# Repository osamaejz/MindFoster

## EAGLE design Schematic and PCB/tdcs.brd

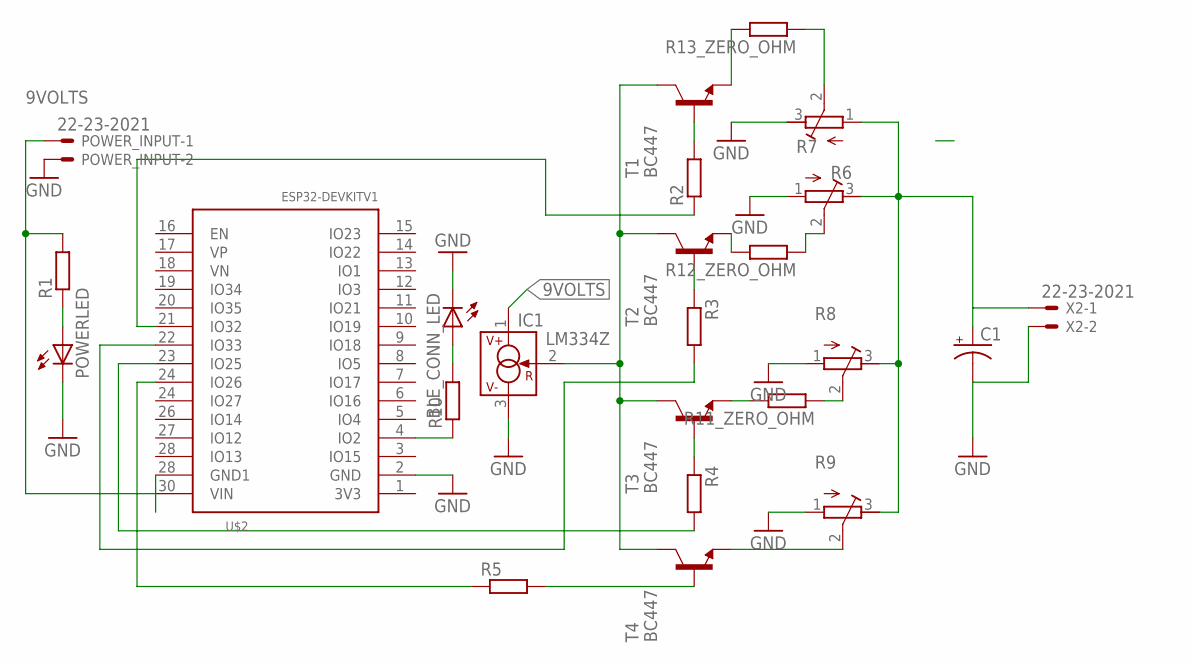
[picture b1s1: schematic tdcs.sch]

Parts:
BLE_CONN_LED: LED3MM
C1: CPOL-USE1.8-4; E1,8-4
IC1: LM334Z; TO92
POWERLED: LEDB152; Q62902-B152
POWER_INPUT: 22-23-2021
R1, R2, R3, R4, R5, R10, R11_ZERO_OHM, R12_ZERO_OHM, R13_ZERO_OHM: R-EU_0204/5; 0204/5
R6, R7, R8, R9: R-TRIMM64W; RTRIM64W
T1, T2, T3, T4: BC447; TO92-EBC
U$2: ESP32DEVKITV1; ESP32-DEVKITV1
X2: 22-23-2021

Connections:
9VOLTS: IC1.1 (V+), POWER_INPUT.1, R1.2, U$2.30 (VIN)
GND: BLE_CONN_LED.K (C), C1.-, IC1.3 (V-), POWERLED.K (C), POWER_INPUT.2, R6.3 (E), R7.1 (A), R8.1 (A), R9.1 (A), U$2.2 (GND), X2.2
unnamed: R2.2, T1.B
unnamed: R3.1, T2.B
unnamed: R4.1, T3.B
unnamed: R5.1, U$2.24 (IO27)
unnamed: IC1.2 (R), T1.C, T2.C, T3.C, T4.C
unnamed: BLE_CONN_LED.A, R10.2
unnamed: R3.2, U$2.22 (IO33)
unnamed: R4.2, U$2.23 (IO25)
unnamed: R5.2, T4.B
unnamed: R9.2 (S), T4.E
unnamed: R11_ZERO_OHM.2, T3.E
unnamed: R7.2 (S), R12_ZERO_OHM.1
unnamed: C1.+, R6.1 (A), R7.3 (E), R8.3 (E), R9.3 (E), X2.1
unnamed: R10.1, U$2.4 (IO2)
unnamed: POWERLED.A, R1.1
unnamed: R8.2 (S), R11_ZERO_OHM.1
unnamed: R12_ZERO_OHM.2, T2.E
unnamed: R13_ZERO_OHM.2, T1.E
unnamed: R6.2 (S), R13_ZERO_OHM.1
unnamed: R2.1, U$2.21 (IO32)

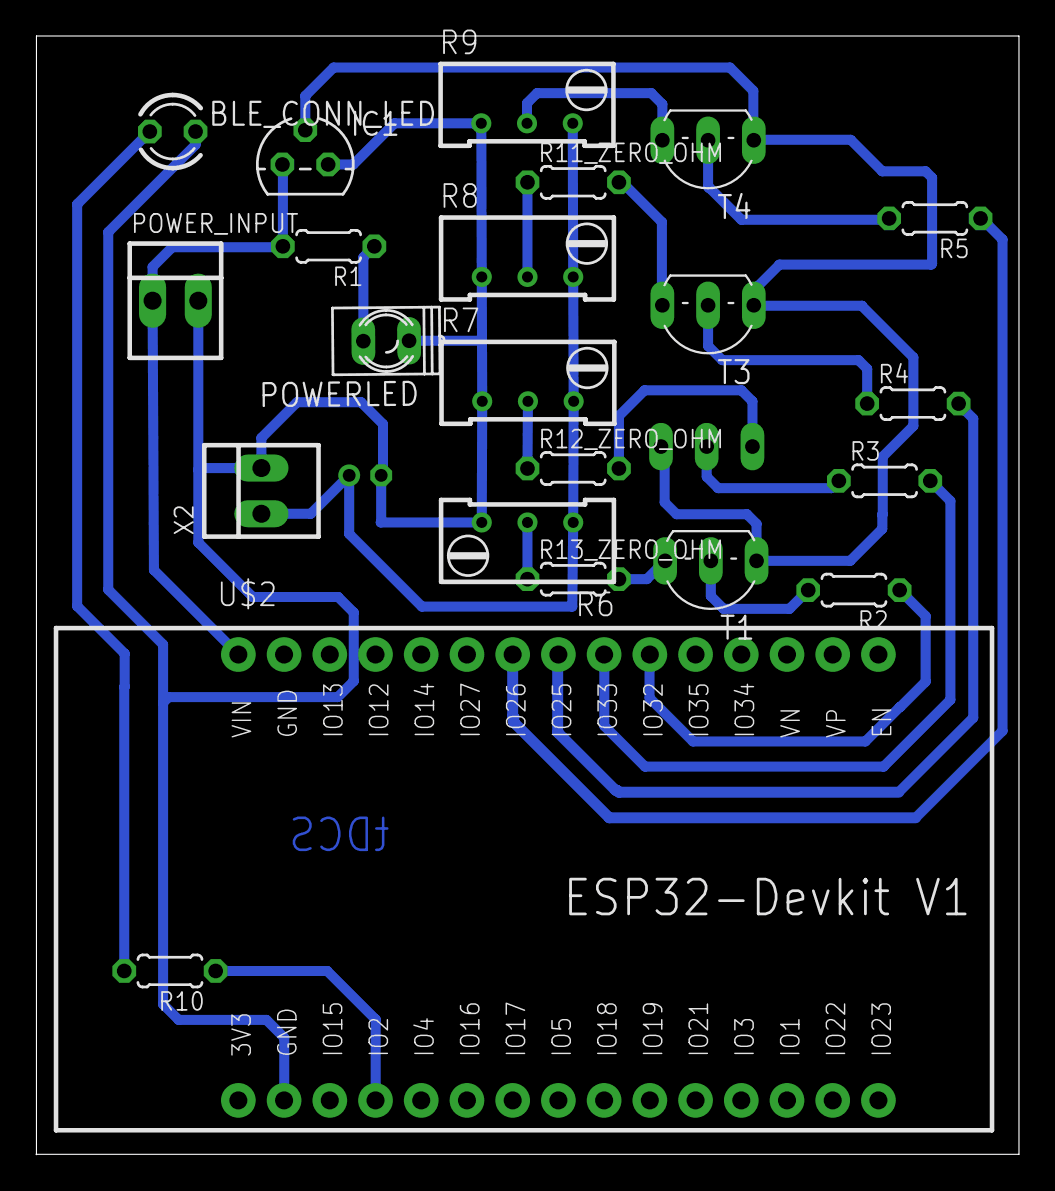
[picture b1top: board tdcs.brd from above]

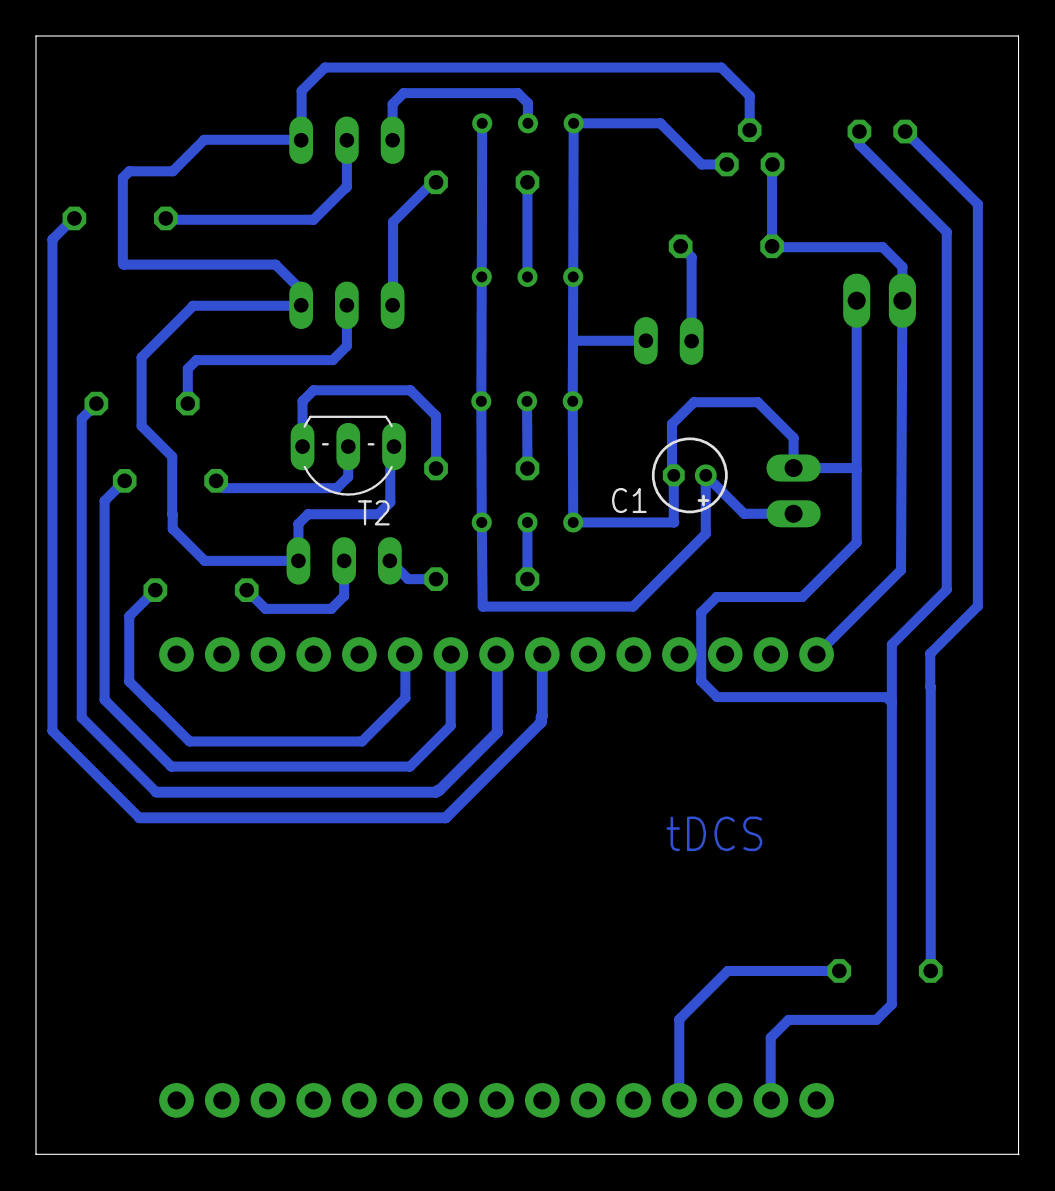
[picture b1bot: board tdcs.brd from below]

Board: 2 copper layers, 54.6 x 62.2 mm, 24 parts (2 on the bottom side), 22 nets.

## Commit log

2023-10-10 MF Android Code
2023-10-10 MF Complete
2023-10-10 APK file
2023-10-11 files from git ignore
